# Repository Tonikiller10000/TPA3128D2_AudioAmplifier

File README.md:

# TPA3128D2_AudioAmplifier

## Description:
This is an guitar audio amplifier made with the TPA3128D2 2x30W class D audio amplifier.<br>
Further documentation will be added uppon testing. For more pictures of the 3D model and the projection, access the [pictures](https://github.com/Tonikiller10000/TPA3128D2_AudioAmplifier/tree/main/TPA3128D2_AMP_Pictures) folder.  

Schematic:

## Links: 
- TPA3128D2 datasheet: https://www.ti.com/lit/ds/symlink/tpa3128d2.pdf?ts=1710324129765&ref_url=https%253A%252F%252Fwww.google.com%252F

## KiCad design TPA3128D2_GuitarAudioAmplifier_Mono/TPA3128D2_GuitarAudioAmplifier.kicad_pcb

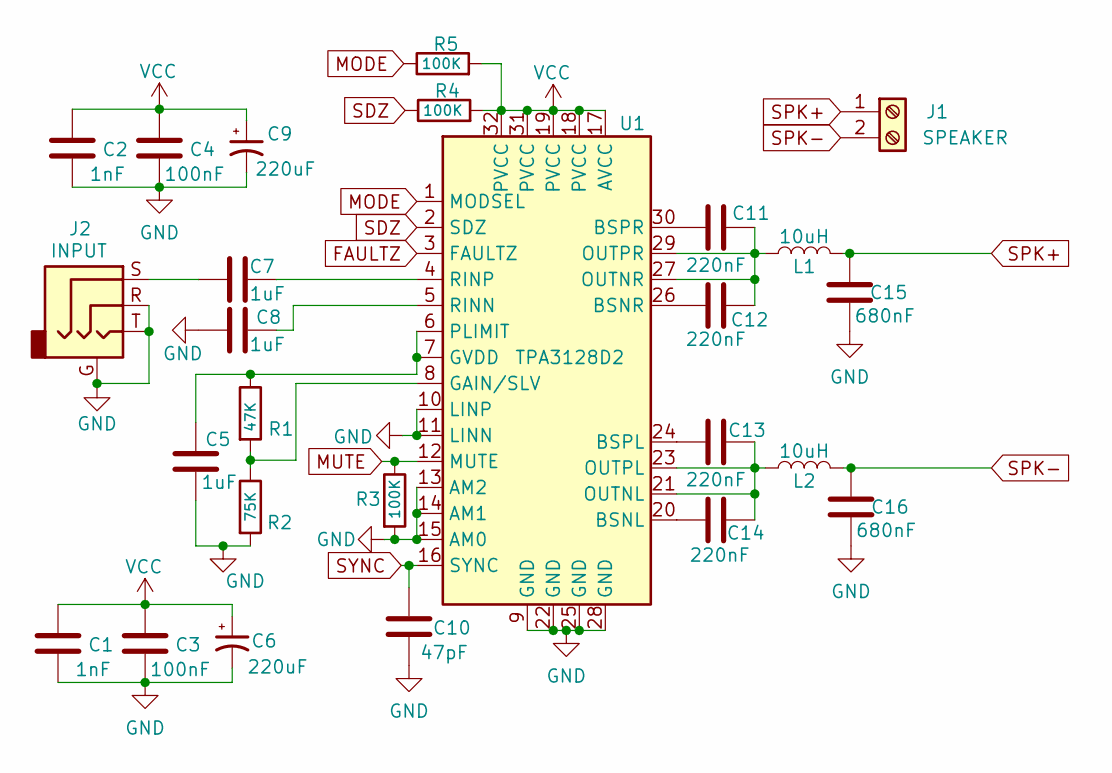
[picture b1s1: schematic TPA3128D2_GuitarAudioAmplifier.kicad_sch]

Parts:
C1, C2: 1nF
C3, C4: 100nF
C5, C7, C8: 1uF
C6, C9: 220uF
C10: 47pF
C11, C12, C13, C14: 220nF
C15, C16: 680nF
J1: SPEAKER
J2: INPUT; Jack_6.35mm_Neutrik_NRJ3HF-1_Horizontal
L1, L2: 10uH
R1: 47K
R2: 75K
R3, R4, R5: 100K
U1: TPA3128D2; HTSSOP-32-1EP_6.1x11mm_P0.65mm_EP5.2x11mm_Mask4.11x4.36mm

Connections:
FAULTZ: U1.3 (FAULTZ)
GND: C1.1, C2.1, C3.1, C4.1, C5.2, C6.2, C8.2, C9.2, C10.1, C15.1, C16.1, J2.G, J2.R, J2.T, R2.2, R3.2, U1.9 (GND), U1.10 (LINP), U1.11 (LINN), U1.13 (AM2), U1.14 (AM1), U1.15 (AM0), U1.22 (GND), U1.25 (GND), U1.28 (GND), U1.33; also elsewhere on the board
MODE: R5.1, U1.1 (MODSEL); also elsewhere on the board
MUTE: R3.1, U1.12 (MUTE)
unnamed: C7.2, J2.S
unnamed: C14.1, U1.20 (BSNL)
unnamed: C12.1, U1.26 (BSNR)
unnamed: C13.1, U1.24 (BSPL)
unnamed: C11.1, U1.30 (BSPR)
unnamed: R1.2, R2.1, U1.8 (GAIN/SLV)
unnamed: C5.1, R1.1, U1.6 (PLIMIT), U1.7 (GVDD)
unnamed: C13.2, C14.2, L2.1, U1.21 (OUTNL), U1.23 (OUTPL)
unnamed: C11.2, C12.2, L1.1, U1.27 (OUTNR), U1.29 (OUTPR)
unnamed: C8.1, U1.5 (RINN)
unnamed: C7.1, U1.4 (RINP)
SDZ: R4.1, U1.2 (SDZ); also elsewhere on the board
SPK+: C15.2, J1.1, L1.2
SPK-: C16.2, J1.2, L2.2
SYNC: C10.2, U1.16 (SYNC)
VCC: C1.2, C2.2, C3.2, C4.2, C6.1, C9.1, R4.2, R5.2, U1.17 (AVCC), U1.18 (PVCC), U1.19 (PVCC), U1.31 (PVCC), U1.32 (PVCC); also elsewhere on the board

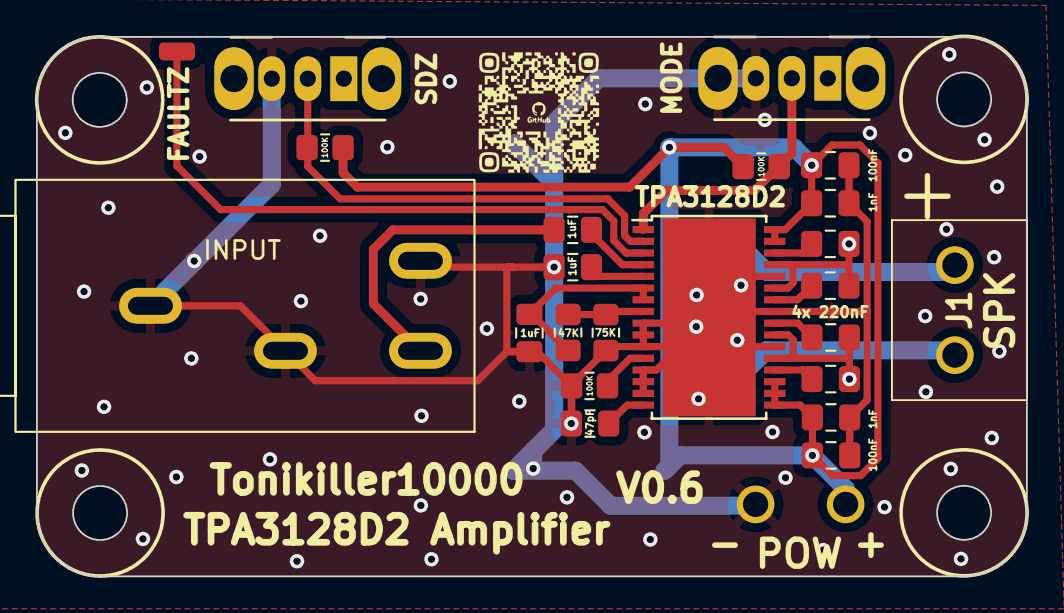
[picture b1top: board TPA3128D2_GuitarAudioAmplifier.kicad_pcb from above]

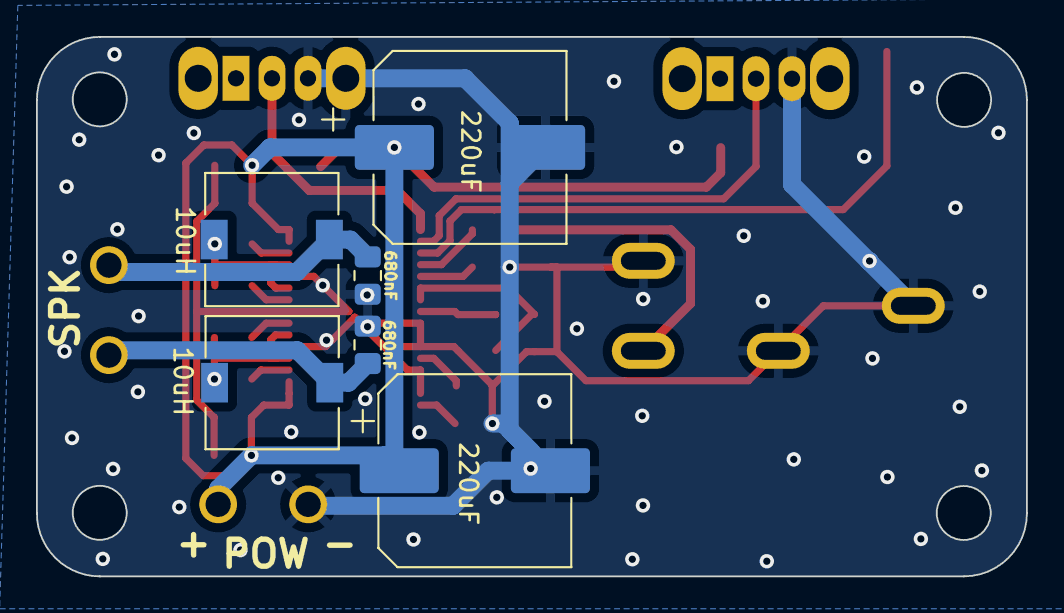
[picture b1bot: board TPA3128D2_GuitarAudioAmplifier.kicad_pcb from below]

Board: 2 copper layers, 55.0 x 30.0 mm, 29 parts (7 on the bottom side), 19 nets.

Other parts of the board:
J1#2: SPEAKER; KF3012P
SW1, SW1#2: SW_SPDT; SW_CuK_OS102011MA1QN1_SPDT_Angled

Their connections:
GND: J1#2.2, SW1.3 (C), SW1#2.3 (C); also elsewhere on the board
MODE: SW1.2 (B); also elsewhere on the board
SDZ: SW1#2.2 (B); also elsewhere on the board
VCC: J1#2.1; also elsewhere on the board

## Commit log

2024-03-06 init
